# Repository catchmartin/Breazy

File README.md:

Breazy
======

The personal pollution exposure monitor. Making the invisible, visible!

## Setting up Ionic Framework for Mobile App

1. http://nodejs.org/download/
2. Android SDK - https://developer.android.com/sdk/index.html
3. Apache Ant - http://ant.apache.org/bindownload.cgi
4. Java SDK - http://www.oracle.com/technetwork/java/javase/index.html
5. `JAVA_HOME` and `ANDROID_HOME` environment variables configured
6. Ant on the `PATH`
7. `git clone https://github.com/catchmartin/Breazy.git`
8. `cd Breazy/App`
9. `rm -r mobile-treo`
7. `npm install -g cordova ionic`
8. `ionic start mobile-treo sidemenu`
9. `cd mobile-treo`
10. `ionic platform add android`
11. `git reset --hard HEAD`

notes: On a linux(Ubuntu 14.04 x64) I found that I had to install 2 packages to build/run the android app:

1. sudo apt-get install lib32z1
2. sudo apt-get install lib32stdc++6

## Setting up the NodeRed server

1. http://nodejs.org/download/
1. http://nodered.org/docs/getting-started/installation.html
  * https://github.com/node-red/node-red-nodes
  * npm install mongodb
    * configure mongodb if necessary
      * cd ~/Breazy/Backend/mongodb
      * mongorestore
      * cd ~/node-red*
  * cd nodes/; git clone https://github.com/node-red/node-red-nodes.git
  * cd ..
  * copy in breazy.json file
  * edit settings.js file for CORS https://groups.google.com/d/msg/node-red/9ZZY_2xcfaI/MHlgty0xQrcJ
  * node red.js breazy.json
  
## Scraping Info
1. Weather
  1. Accuweather
  2. WeatheUnderground
    * http://www.wunderground.com/weather/api/
    * http://www.wunderground.com/weather/api/d/docs
    * GET http://api.wunderground.com/api/Your_Key/features/settings/q/query.format
    * http://www.wunderground.com/weather/api/d/docs?d=data/index&MR=1
    * treo
    * http://api.wunderground.com/api/$KEY/forecast/geolookup/conditions/q/CA/San_Francisco.json
2. Sensor
  1. London Air Quality
    * http://api.erg.kcl.ac.uk/AirQuality/help

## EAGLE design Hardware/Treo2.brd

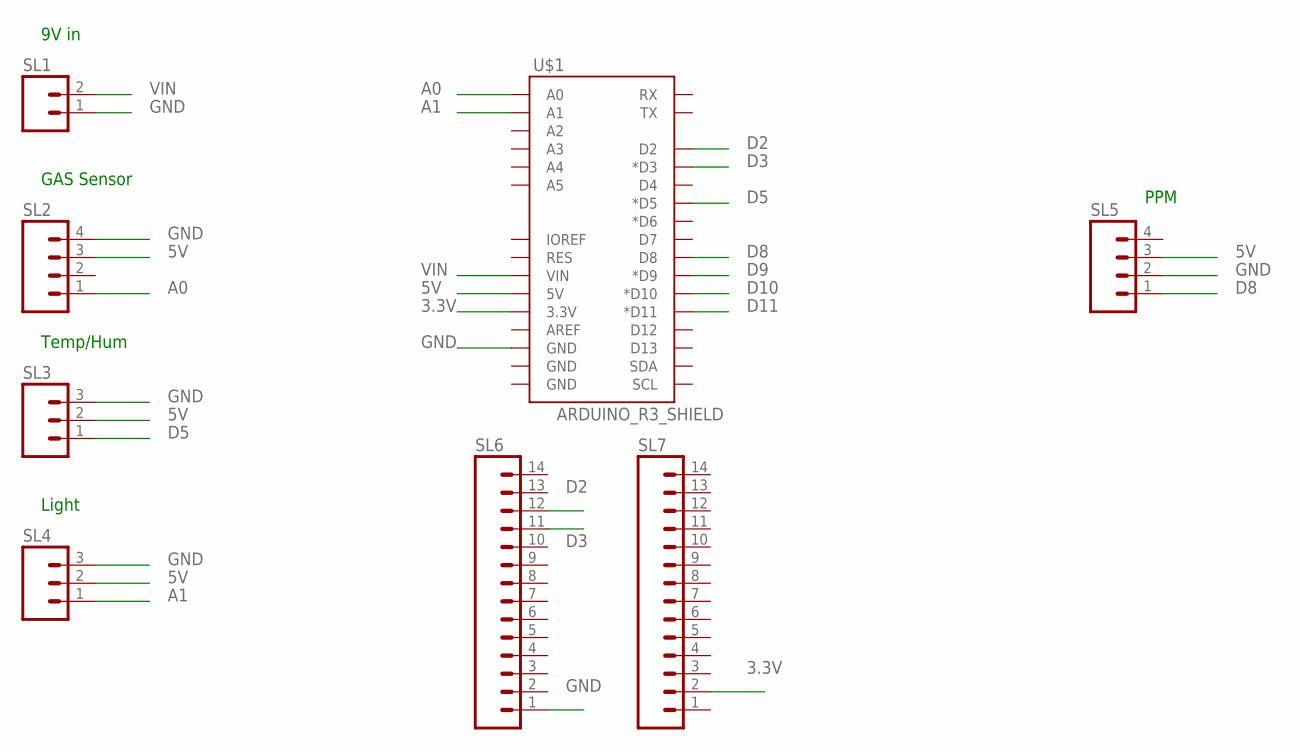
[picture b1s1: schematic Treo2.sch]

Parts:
SL1: M02; 02P
SL2, SL5: M04; 04P
SL3, SL4: M03; 03P
SL6, SL7: M14; 14P
U$1: ARDUINO_R3_SHIELD; UNO_R3_SHIELD

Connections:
3.3V: SL7.2, U$1.3.3V
5V: SL2.3, SL3.2, SL4.2, SL5.3, U$1.5V
A0: SL2.1, U$1.A0
A1: SL4.1, U$1.A1
D2: SL6.12, U$1.D2
D3: SL6.11, U$1.D3 (*D3)
D5: SL3.1, U$1.D5 (*D5)
D8: SL5.1, U$1.D8
D9: U$1.D9 (*D9)
D10: U$1.D10 (*D10)
D11: U$1.D11 (*D11)
GND: SL1.1, SL2.4, SL3.3, SL4.3, SL5.2, SL6.1, U$1.GND@2 (GND)
VIN: SL1.2, U$1.VIN

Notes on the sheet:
GAS Sensor
9V in
Temp/Hum
Light
PPM

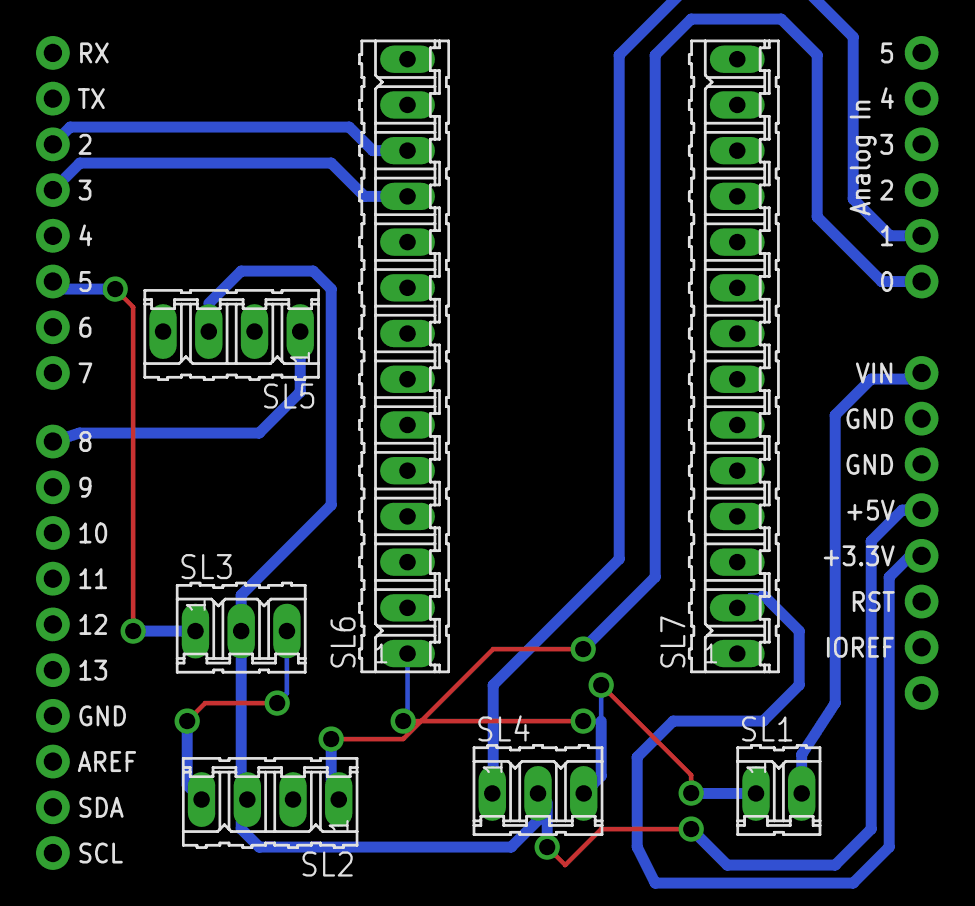
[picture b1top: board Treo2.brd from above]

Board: 2 copper layers, 8 parts (0 on the bottom side), 10 nets.

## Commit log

2014-11-02 Added Ionic mobile app directory
2014-11-02 Renaming mobile app directory
2014-11-02 Added a logo, more to follow
2014-11-02 Added android icons
2014-11-02 initial nodered sketch. scrape weather and airquality.
2014-11-02 New folder for Arduino code
2014-11-02 Code used for testing sensors on MCUs
    These are codes that are used for testing sensors and also the
    RedBearLab Blend Micro
2014-11-02 added read, write apis and scrape functions
2014-11-02 TODO figure how to commit path to sym link. Removed the sym link and added the actual file.
2014-11-02 updated mobile app files. Not working yet.
2014-11-03 Schematics updated
2014-11-03 Code used for testing sensors on MCUs
    Code used for testing sensors on MCUs on the Treo system
2014-11-03 Added magic Treo Algorithm
2014-11-03 Updated app
2014-11-04 Prototype presentation version
2014-11-06 API calls working from ionic App. Temperature and Humidity data being graphed as a placeholder.
2014-11-06 Rebuilding apk files for working with Rest API
2014-11-08 add cnc gcode & designs/code for docking station
2014-11-11 Added backup files for mongo db
2014-11-11 Update settings.js
    Added password protection for the NodeRed admin page.
2014-11-11 Update README.md
    Updated instructions for importing Treo database into new MongoDB
2014-11-15 added notes on linux install.

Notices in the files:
parts and their libraries:
SparkFun-Boards: Licensing: CC v3.0 Share-Alike You are welcome to use this library for commercial purposes.
